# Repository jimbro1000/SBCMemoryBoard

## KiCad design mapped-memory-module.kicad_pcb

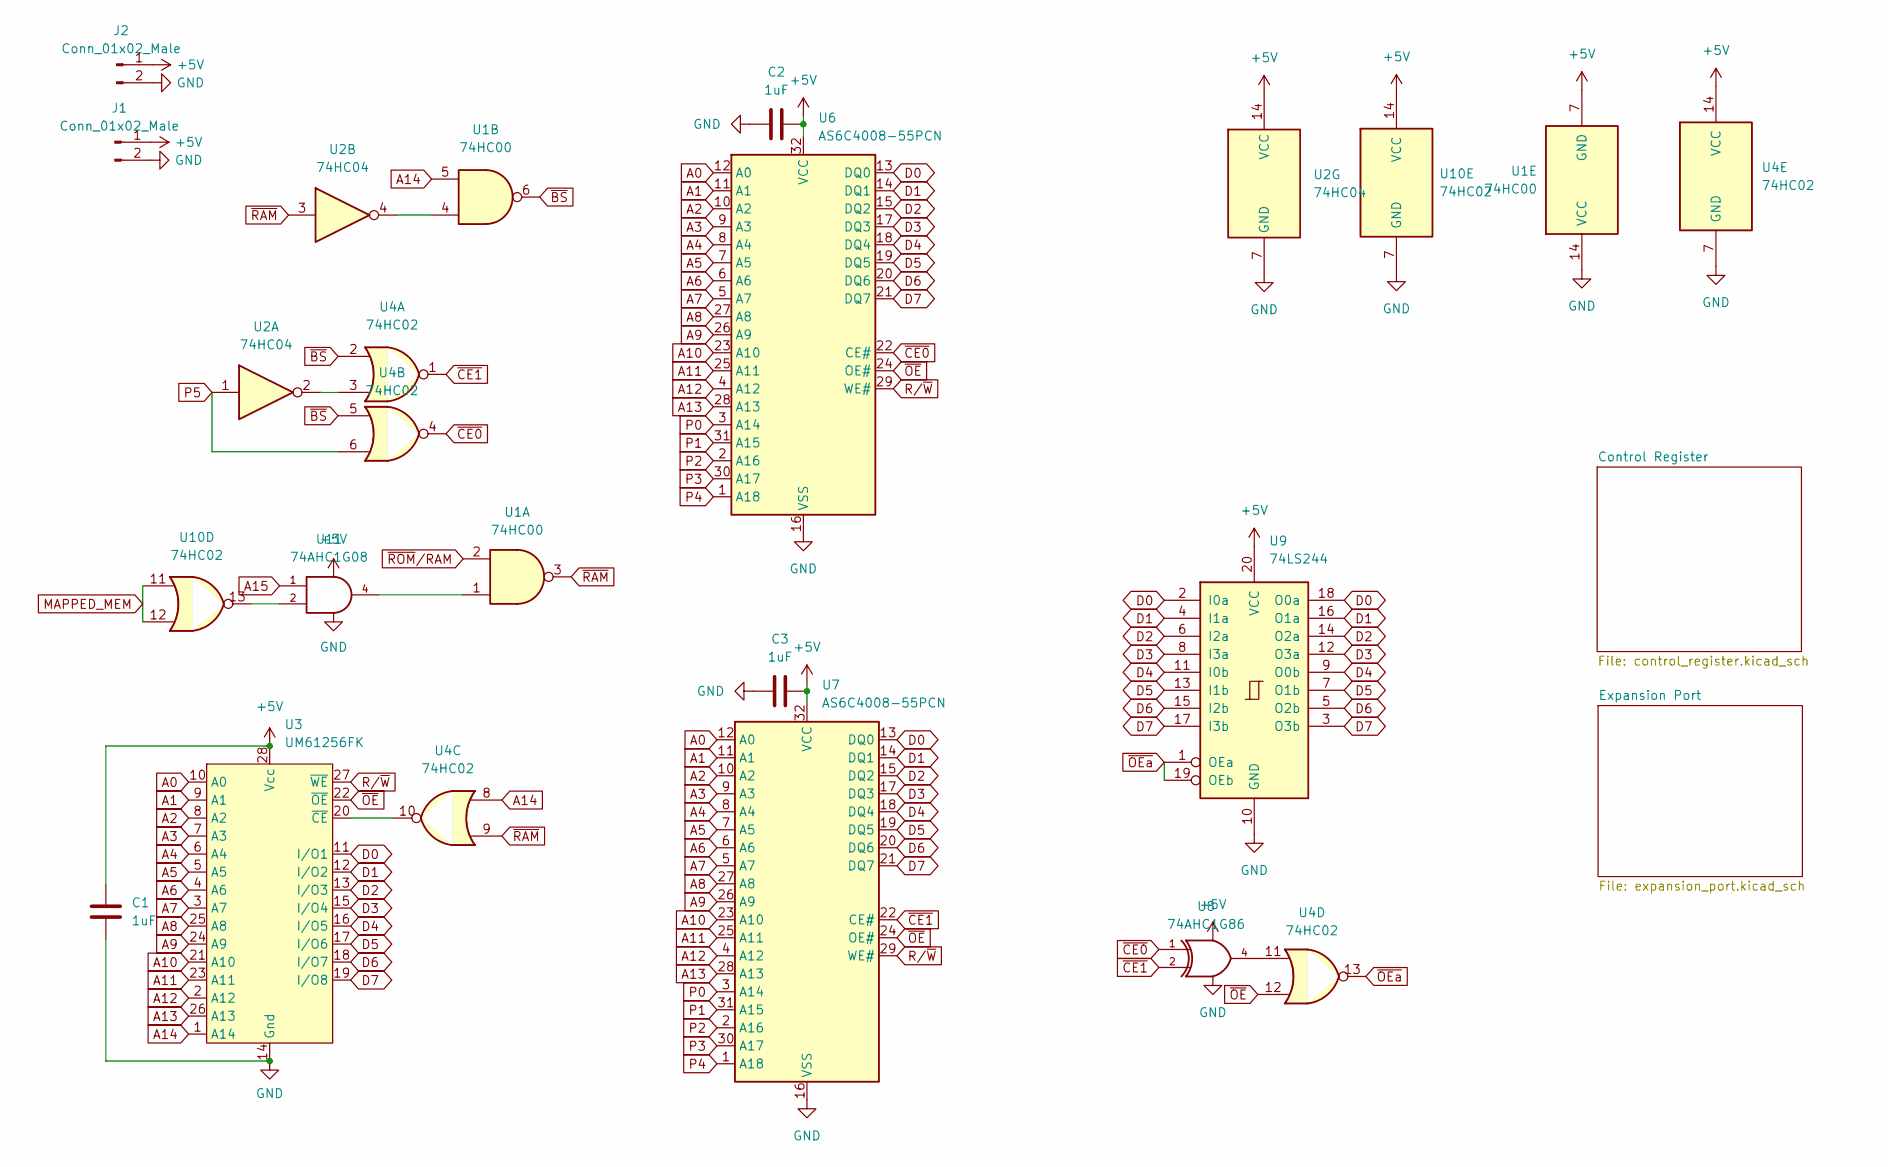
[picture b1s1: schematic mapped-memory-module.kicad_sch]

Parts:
C1, C2, C3: 1uF; C_0805_2012Metric
J1, J2: Conn_01x02_Male; PinHeader_1x02_P2.54mm_Vertical
U1: 74HC00; SO-14_3.9x8.65mm_P1.27mm
U2: 74HC04; SO-14_3.9x8.65mm_P1.27mm
U3: UM61256FK; DIP-28_W7.62mm
U4, U10: 74HC02; SO-14_3.9x8.65mm_P1.27mm
U6, U7: AS6C4008-55PCN; SSOP-32_11.305x20.495mm_P1.27mm
U8: 74AHC1G86; TSOP-5_1.65x3.05mm_P0.95mm
U9: 74LS244; SO-20_5.3x12.6mm_P1.27mm
U11: 74AHC1G08; TSOP-5_1.65x3.05mm_P0.95mm

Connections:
+5V: C1.1, C2.1, C3.1, J1.1, J2.1, U1.7 (GND), U2.14 (VCC), U3.28 (Vcc), U4.14 (VCC), U6.32 (VCC), U7.32 (VCC), U8.5 (VCC), U9.20 (VCC), U10.14 (VCC), U11.5 (VCC); also elsewhere on the board
A0: U3.10 (A0), U6.12 (A0), U7.12 (A0); also elsewhere on the board
A1: U3.9 (A1), U6.11 (A1), U7.11 (A1); also elsewhere on the board
A2: U3.8 (A2), U6.10 (A2), U7.10 (A2); also elsewhere on the board
A3: U3.7 (A3), U6.9 (A3), U7.9 (A3); also elsewhere on the board
A4: U3.6 (A4), U6.8 (A4), U7.8 (A4); also elsewhere on the board
A5: U3.5 (A5), U6.7 (A5), U7.7 (A5); also elsewhere on the board
A6: U3.4 (A6), U6.6 (A6), U7.6 (A6); also elsewhere on the board
A7: U3.3 (A7), U6.5 (A7), U7.5 (A7); also elsewhere on the board
A8: U3.25 (A8), U6.27 (A8), U7.27 (A8); also elsewhere on the board
A9: U3.24 (A9), U6.26 (A9), U7.26 (A9); also elsewhere on the board
A10: U3.21 (A10), U6.23 (A10), U7.23 (A10); also elsewhere on the board
A11: U3.23 (A11), U6.25 (A11), U7.25 (A11); also elsewhere on the board
A12: U3.2 (A12), U6.4 (A12), U7.4 (A12); also elsewhere on the board
A13: U3.26 (A13), U6.28 (A13), U7.28 (A13); also elsewhere on the board
A14: U1.5, U3.1 (A14), U4.8; also elsewhere on the board
A15: U11.1; also elsewhere on the board
D0: U3.11 (I/O1), U6.13 (DQ0), U7.13 (DQ0), U9.2 (I0a), U9.18 (O0a); also elsewhere on the board
D1: U3.12 (I/O2), U6.14 (DQ1), U7.14 (DQ1), U9.4 (I1a), U9.16 (O1a); also elsewhere on the board
D2: U3.13 (I/O3), U6.15 (DQ2), U7.15 (DQ2), U9.6 (I2a), U9.14 (O2a); also elsewhere on the board
D3: U3.15 (I/O4), U6.17 (DQ3), U7.17 (DQ3), U9.8 (I3a), U9.12 (O3a); also elsewhere on the board
D4: U3.16 (I/O5), U6.18 (DQ4), U7.18 (DQ4), U9.9 (O0b), U9.11 (I0b); also elsewhere on the board
D5: U3.17 (I/O6), U6.19 (DQ5), U7.19 (DQ5), U9.7 (O1b), U9.13 (I1b); also elsewhere on the board
D6: U3.18 (I/O7), U6.20 (DQ6), U7.20 (DQ6), U9.5 (O2b), U9.15 (I2b); also elsewhere on the board
D7: U3.19 (I/O8), U6.21 (DQ7), U7.21 (DQ7), U9.3 (O3b), U9.17 (I3b); also elsewhere on the board
GND: C1.2, C2.2, C3.2, J1.2, J2.2, U1.14 (VCC), U2.7 (GND), U3.14 (Gnd), U4.7 (GND), U6.16 (VSS), U7.16 (VSS), U8.3 (GND), U9.10 (GND), U10.7 (GND), U11.3 (GND); also elsewhere on the board
MAPPED_MEM: U10.11, U10.12; also elsewhere on the board
unnamed: U1.1, U11.4
unnamed: U1.4, U2.4
unnamed: U2.2, U4.3
unnamed: U3.20 (~CE), U4.10
unnamed: U4.11, U8.4
unnamed: U10.13, U11.2
P0: U6.3 (A14), U7.3 (A14); also elsewhere on the board
P1: U6.31 (A15), U7.31 (A15); also elsewhere on the board
P2: U6.2 (A16), U7.2 (A16); also elsewhere on the board
P3: U6.30 (A17), U7.30 (A17); also elsewhere on the board
P4: U6.1 (A18), U7.1 (A18); also elsewhere on the board
P5: U2.1, U4.6; also elsewhere on the board
R/~W: U3.27 (~WE), U6.29 (WE#), U7.29 (WE#); also elsewhere on the board
~BS: U1.6, U4.2, U4.5
~CE0: U4.4, U6.22 (CE#), U8.1
~CE1: U4.1, U7.22 (CE#), U8.2
~OEa: U4.13, U9.1 (OEa), U9.19 (OEb)
~OE: U3.22 (~OE), U4.12, U6.24 (OE#), U7.24 (OE#)
~RAM: U1.3, U2.3, U4.9
~ROM/RAM: U1.2

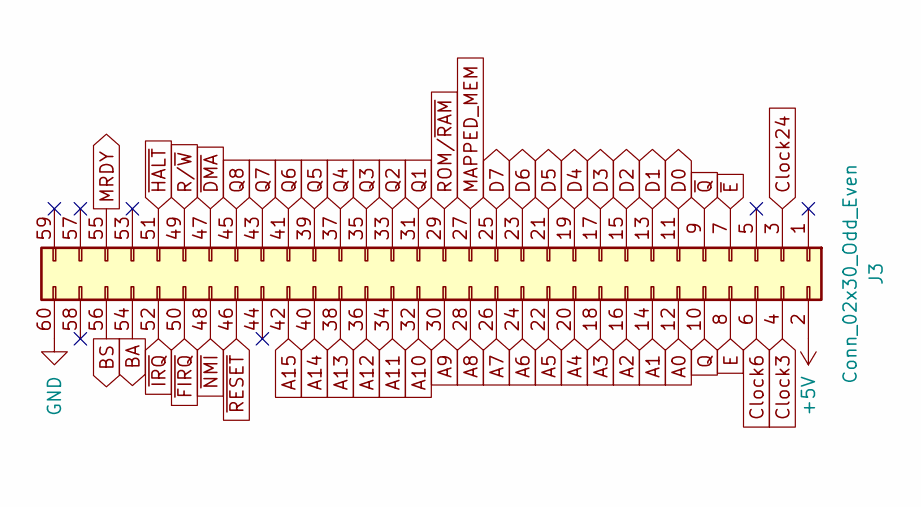
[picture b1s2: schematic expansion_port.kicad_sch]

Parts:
J3: Conn_02x30_Odd_Even; PinHeader_2x30_P2.54mm_Vertical

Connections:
+5V: J3.2; also elsewhere on the board
A0: J3.12; also elsewhere on the board
A1: J3.14; also elsewhere on the board
A2: J3.16; also elsewhere on the board
A3: J3.18; also elsewhere on the board
A4: J3.20; also elsewhere on the board
A5: J3.22; also elsewhere on the board
A6: J3.24; also elsewhere on the board
A7: J3.26; also elsewhere on the board
A8: J3.28; also elsewhere on the board
A9: J3.30; also elsewhere on the board
A10: J3.32; also elsewhere on the board
A11: J3.34; also elsewhere on the board
A12: J3.36; also elsewhere on the board
A13: J3.38; also elsewhere on the board
A14: J3.40; also elsewhere on the board
A15: J3.42; also elsewhere on the board
BA: J3.54
BS: J3.56
Clock3: J3.4
Clock6: J3.6
Clock24: J3.3
D0: J3.11; also elsewhere on the board
D1: J3.13; also elsewhere on the board
D2: J3.15; also elsewhere on the board
D3: J3.17; also elsewhere on the board
D4: J3.19; also elsewhere on the board
D5: J3.21; also elsewhere on the board
D6: J3.23; also elsewhere on the board
D7: J3.25; also elsewhere on the board
E: J3.8
GND: J3.60; also elsewhere on the board
MAPPED_MEM: J3.27; also elsewhere on the board
MRDY: J3.55
Q: J3.10
Q1: J3.31
Q2: J3.33
Q3: J3.35
Q4: J3.37
Q5: J3.39
Q6: J3.41
Q7: J3.43
Q8: J3.45
ROM/~RAM: J3.29
R/~W: J3.49; also elsewhere on the board
~DMA: J3.47
~E: J3.7
~FIRQ: J3.50
~HALT: J3.51
~IRQ: J3.52
~NMI: J3.48
~Q: J3.9
~RESET: J3.46

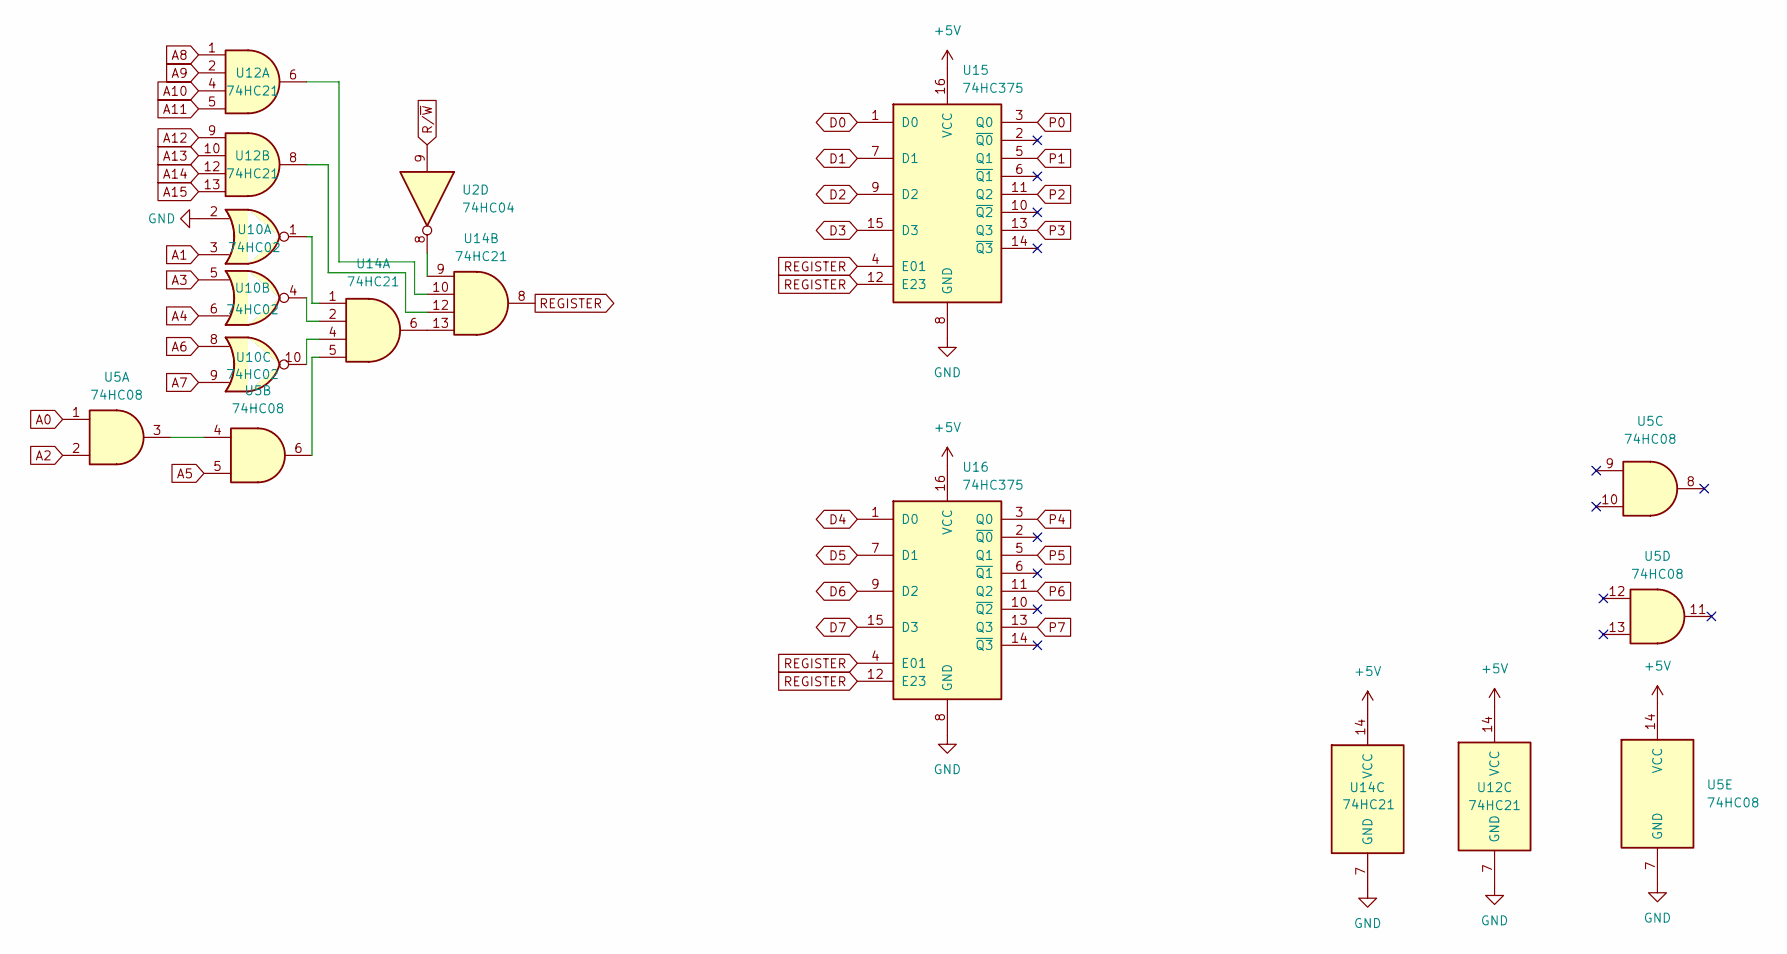
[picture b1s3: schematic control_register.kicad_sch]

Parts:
U2: 74HC04; SO-14_3.9x8.65mm_P1.27mm
U5: 74HC08; SO-14_3.9x8.65mm_P1.27mm
U10: 74HC02; SO-14_3.9x8.65mm_P1.27mm
U12, U14: 74HC21; SO-14_3.9x8.65mm_P1.27mm
U15, U16: 74HC375; SO-16_3.9x9.9mm_P1.27mm

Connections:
+5V: U5.14 (VCC), U12.14 (VCC), U14.14 (VCC), U15.16 (VCC), U16.16 (VCC); also elsewhere on the board
A0: U5.1; also elsewhere on the board
A1: U10.3; also elsewhere on the board
A2: U5.2; also elsewhere on the board
A3: U10.5; also elsewhere on the board
A4: U10.6; also elsewhere on the board
A5: U5.5; also elsewhere on the board
A6: U10.8; also elsewhere on the board
A7: U10.9; also elsewhere on the board
A8: U12.1; also elsewhere on the board
A9: U12.2; also elsewhere on the board
A10: U12.4; also elsewhere on the board
A11: U12.5; also elsewhere on the board
A12: U12.9; also elsewhere on the board
A13: U12.10; also elsewhere on the board
A14: U12.12; also elsewhere on the board
A15: U12.13; also elsewhere on the board
D0: U15.1 (D0); also elsewhere on the board
D1: U15.7 (D1); also elsewhere on the board
D2: U15.9 (D2); also elsewhere on the board
D3: U15.15 (D3); also elsewhere on the board
D4: U16.1 (D0); also elsewhere on the board
D5: U16.7 (D1); also elsewhere on the board
D6: U16.9 (D2); also elsewhere on the board
D7: U16.15 (D3); also elsewhere on the board
GND: U5.7 (GND), U10.2, U12.7 (GND), U14.7 (GND), U15.8 (GND), U16.8 (GND); also elsewhere on the board
unnamed: U5.3, U5.4
unnamed: U10.1, U14.1
unnamed: U10.4, U14.2
unnamed: U10.10, U14.4
unnamed: U12.6, U14.10
unnamed: U12.8, U14.12
unnamed: U5.6, U14.5
unnamed: U2.8, U14.9
unnamed: U14.6, U14.13
P0: U15.3 (Q0); also elsewhere on the board
P1: U15.5 (Q1); also elsewhere on the board
P2: U15.11 (Q2); also elsewhere on the board
P3: U15.13 (Q3); also elsewhere on the board
P4: U16.3 (Q0); also elsewhere on the board
P5: U16.5 (Q1); also elsewhere on the board
P6: U16.11 (Q2)
P7: U16.13 (Q3)
REGISTER: U14.8, U15.4 (E01), U15.12 (E23), U16.4 (E01), U16.12 (E23)
R/~W: U2.9; also elsewhere on the board

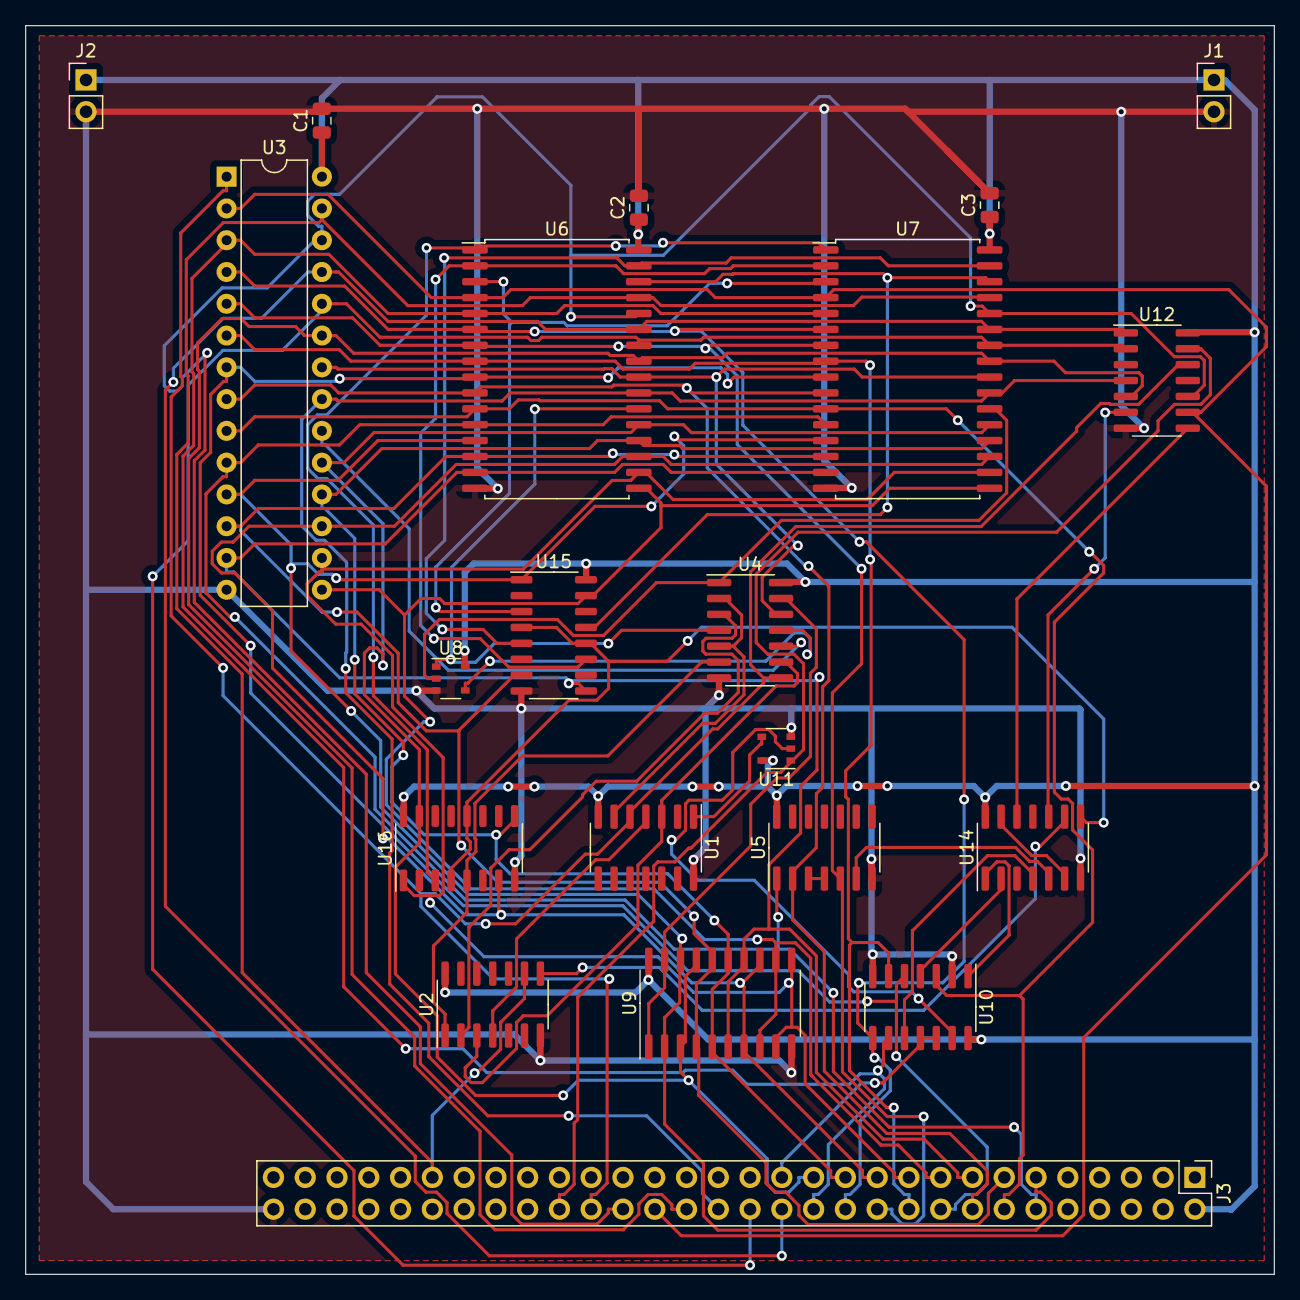
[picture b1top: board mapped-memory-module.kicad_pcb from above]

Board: 2 copper layers, 99.8 x 99.8 mm, 21 parts (0 on the bottom side), 56 nets.

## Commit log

2022-10-06 fit to sbc design standard
2022-10-06 add bom
2022-10-08 add mapped memory lane
